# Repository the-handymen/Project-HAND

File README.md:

# Project-H.A.N.D.
H.A.N.D.: Handy Appendage for Nonlocal Distances

See it in action!
https://www.jonathankornich.com/h-a-n-d-handy-appendage-for-nonloca

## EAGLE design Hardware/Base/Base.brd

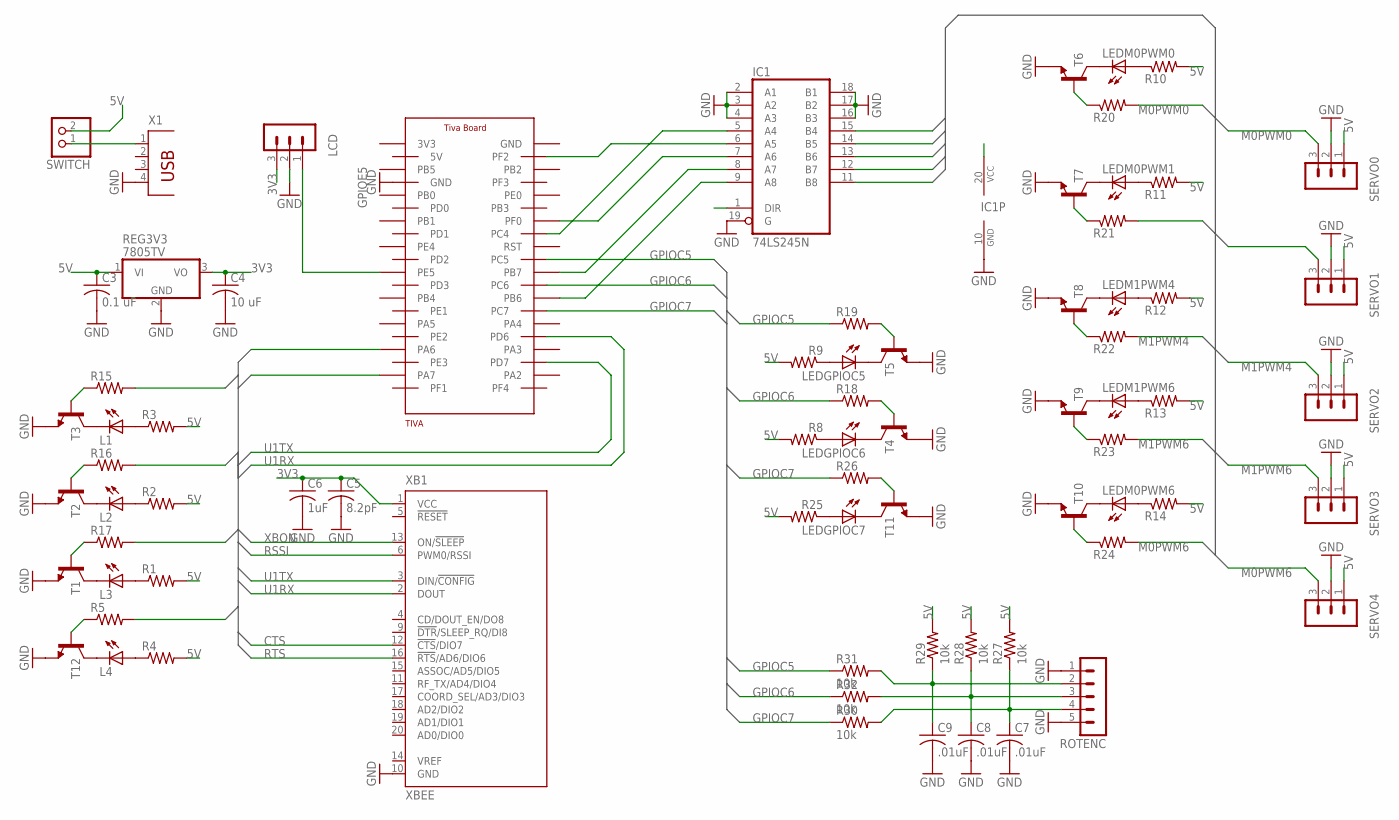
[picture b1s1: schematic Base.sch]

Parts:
C3: 0.1 uF; C025-025X050
C4: 10 uF; C025-025X050
C5: 8.2pF; C025-025X050
C6: 1uF; C025-025X050
C7, C8, C9: .01uF; C025-025X050
IC1: 74LS245N; DIL20
L1, L2, L3, L4: LED5MM
LCD: MA03-1
LEDGPIOC5, LEDGPIOC6, LEDGPIOC7: LED5MM
LEDM0PWM0, LEDM0PWM1, LEDM0PWM6, LEDM1PWM4, LEDM1PWM6: LED5MM
R1, R2, R3, R4, R5, R8, R9, R10, R11, R12, R13, R14, R15, R16, R17, R18, R19, R20, R21, R22, R23, R24, R25, R26: R-US_0207/7; 0207/7
R27, R28, R29, R30, R31, R32: 10k; 0207/7
REG3V3: 7805TV; TO220V
ROTENC: MA05-1
SERVO0, SERVO1, SERVO2, SERVO3, SERVO4: MA03-1
SWITCH: PINHD-1X2; 1X02
T1, T2, T3, T4, T5, T6, T7, T8, T9, T10, T11, T12: 2N3904; TO92
TIVA: TIVA-BOARD
X1: PN87520
XB1: XBEE

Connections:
3V3: C4.1, C5.1, C6.1, LCD.3, REG3V3.3 (VO), XB1.1 (VCC)
5V: C3.1, IC1.1 (DIR), IC1.20 (VCC), R1.2, R2.2, R3.2, R4.2, R8.2, R9.2, R10.2, R11.2, R12.2, R13.2, R14.2, R25.2, R27.2, R28.2, R29.2, REG3V3.1 (VI), SERVO0.1, SERVO1.1, SERVO2.1, SERVO3.1, SERVO4.1, SWITCH.2
CTS: TIVA.PA6, XB1.12 (!CTS!/DIO7)
GND: C3.2, C4.2, C5.2, C6.2, C7.2, C8.2, C9.2, IC1.2 (A1), IC1.3 (A2), IC1.4 (A3), IC1.10 (GND), IC1.16 (B3), IC1.17 (B2), IC1.18 (B1), IC1.19 (G), LCD.2, REG3V3.2 (GND), ROTENC.1, ROTENC.5, SERVO0.2, SERVO1.2, SERVO2.2, SERVO3.2, SERVO4.2, T1.3 (E), T2.3 (E), T3.3 (E), T4.3 (E), T5.3 (E), T6.3 (E), T7.3 (E), T8.3 (E), T9.3 (E), T10.3 (E), T11.3 (E), T12.3 (E), TIVA.GND@1 (GND), X1.4, XB1.10 (GND)
GPIOC5: R19.1, R31.1, TIVA.PC5
GPIOC6: R18.1, R32.1, TIVA.PC6
GPIOC7: R26.1, R30.1, TIVA.PC7
GPIOE5: LCD.1, TIVA.PE5
M0PWM0: IC1.11 (B8), R20.2, SERVO0.3
M0PWM1: IC1.12 (B7), R21.2, SERVO1.3
M0PWM6: IC1.15 (B4), R24.2, SERVO4.3
M1PWM4: IC1.13 (B6), R22.2, SERVO2.3
M1PWM6: IC1.14 (B5), R23.2, SERVO3.3
unnamed: L3.K (C), T1.1 (C)
unnamed: L2.K (C), T2.1 (C)
unnamed: L2.A, R2.1
unnamed: L3.A, R1.1
unnamed: L1.K (C), T3.1 (C)
unnamed: L1.A, R3.1
unnamed: SWITCH.1, X1.1
unnamed: IC1.8 (A7), TIVA.PB7
unnamed: LEDGPIOC6.K (C), T4.1 (C)
unnamed: LEDGPIOC6.A, R8.1
unnamed: LEDGPIOC5.K (C), T5.1 (C)
unnamed: LEDGPIOC5.A, R9.1
unnamed: LEDM0PWM0.K (C), T6.1 (C)
unnamed: LEDM0PWM0.A, R10.1
unnamed: LEDM0PWM1.K (C), T7.1 (C)
unnamed: LEDM0PWM1.A, R11.1
unnamed: LEDM1PWM4.K (C), T8.1 (C)
unnamed: LEDM1PWM4.A, R12.1
unnamed: LEDM1PWM6.K (C), T9.1 (C)
unnamed: LEDM1PWM6.A, R13.1
unnamed: LEDM0PWM6.K (C), T10.1 (C)
unnamed: LEDM0PWM6.A, R14.1
unnamed: R24.1, T10.2 (B)
unnamed: R23.1, T9.2 (B)
unnamed: R22.1, T8.2 (B)
unnamed: R21.1, T7.2 (B)
unnamed: R20.1, T6.2 (B)
unnamed: R15.1, T3.2 (B)
unnamed: R16.1, T2.2 (B)
unnamed: R17.1, T1.2 (B)
unnamed: R18.2, T4.2 (B)
unnamed: R19.2, T5.2 (B)
unnamed: LEDGPIOC7.K (C), T11.1 (C)
unnamed: LEDGPIOC7.A, R25.1
unnamed: R26.2, T11.2 (B)
unnamed: C7.1, R27.1, R30.2, ROTENC.4
unnamed: C8.1, R28.1, R32.2, ROTENC.3
unnamed: C9.1, R29.1, R31.2, ROTENC.2
unnamed: IC1.9 (A8), TIVA.PB6
unnamed: IC1.6 (A5), TIVA.PF2
unnamed: L4.K (C), T12.1 (C)
unnamed: L4.A, R4.1
unnamed: R5.1, T12.2 (B)
unnamed: IC1.7 (A6), TIVA.PF0
unnamed: IC1.5 (A4), TIVA.PC4
RSSI: R5.2, XB1.6 (PWM0/RSSI)
RTS: TIVA.PA7, XB1.16 (!RTS!/AD6/DIO6)
U1RX: R16.2, TIVA.PD6, XB1.2 (DOUT)
U1TX: R17.2, TIVA.PD7, XB1.3 (DIN/!CONFIG)
XBON: R15.2, XB1.13 (ON/!SLEEP)

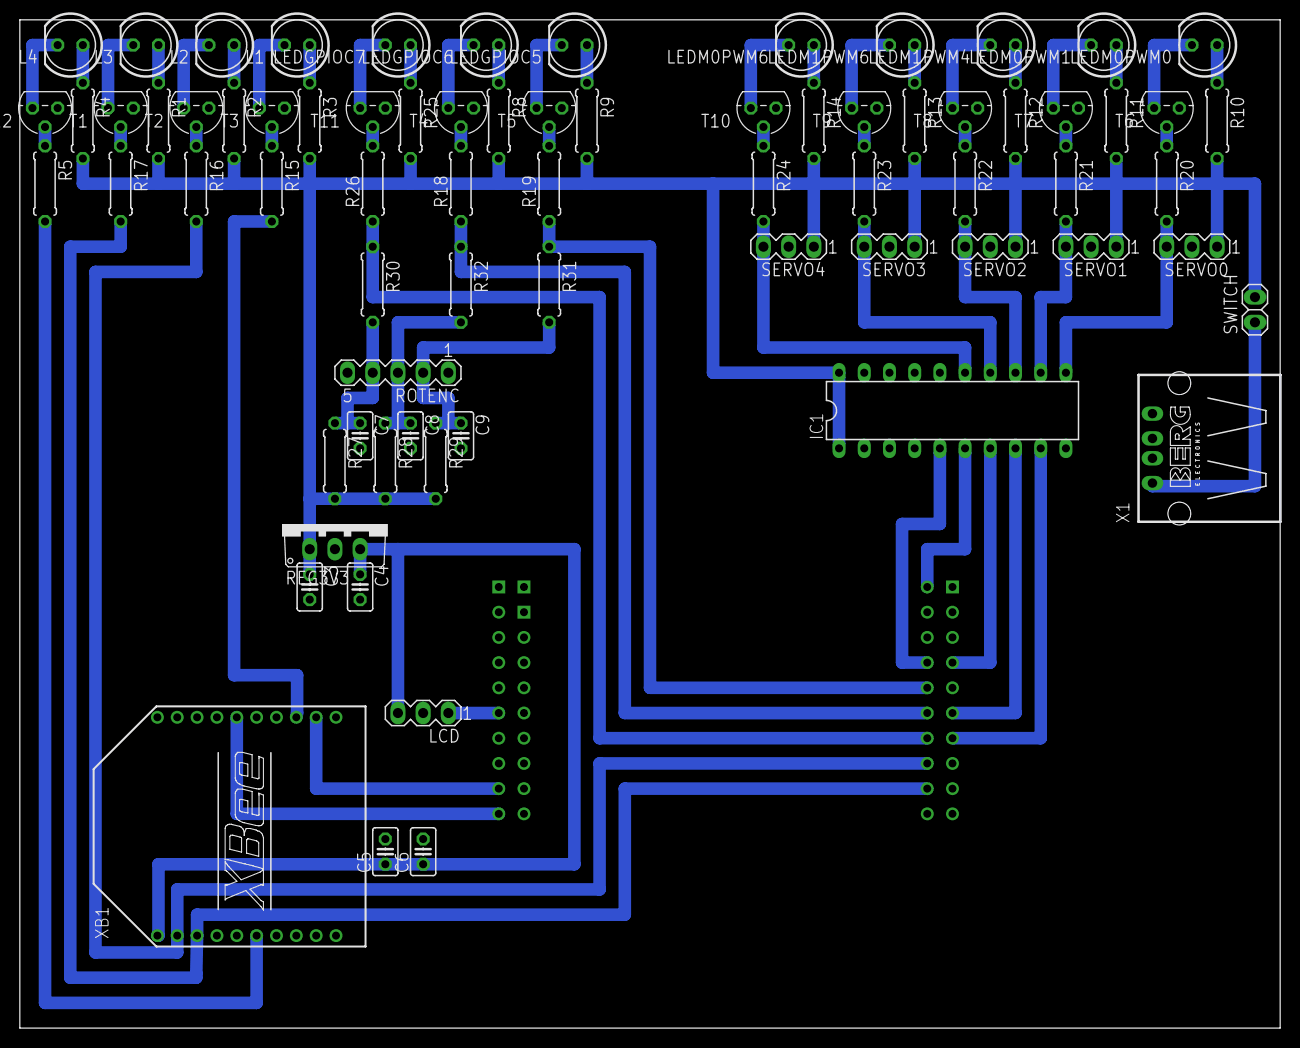
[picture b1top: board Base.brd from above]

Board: 2 copper layers, 127.0 x 101.6 mm, 74 parts (0 on the bottom side), 63 nets.

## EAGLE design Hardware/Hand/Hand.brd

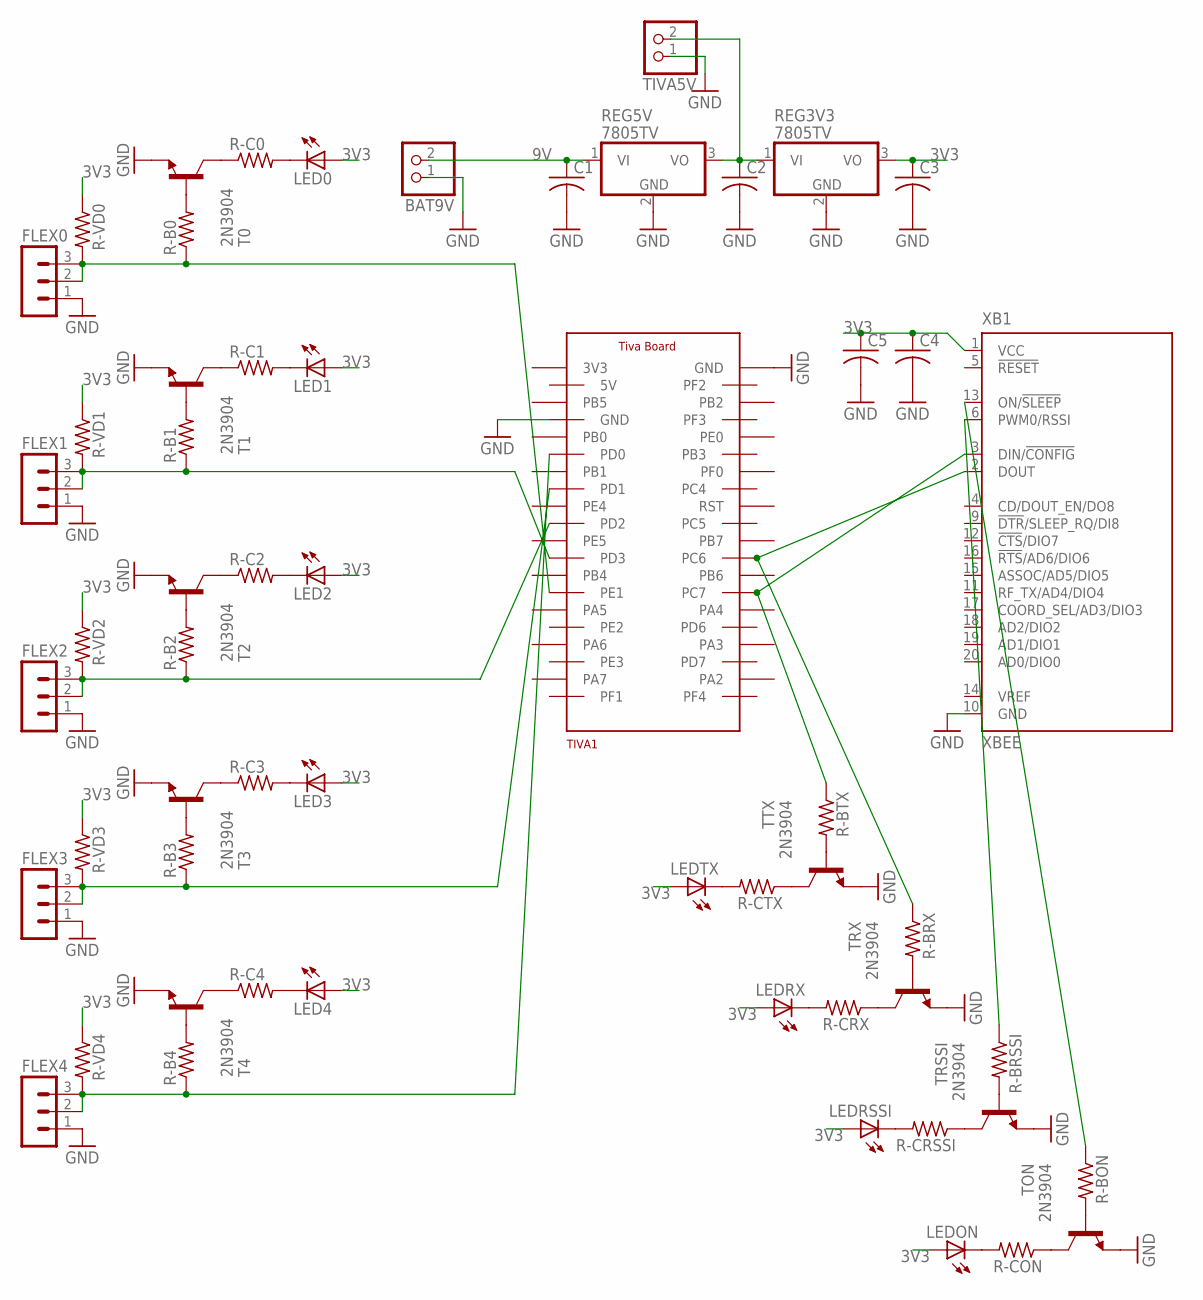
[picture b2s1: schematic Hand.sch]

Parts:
BAT9V: PINHD-1X2; 1X02
C1, C2, C3, C4, C5: C-US025-025X050; C025-025X050
FLEX0, FLEX1, FLEX2, FLEX3, FLEX4: MA03-1
LED0, LED1, LED2, LED3, LED4: LED5MM
LEDON: LED5MM
LEDRSSI: LED5MM
LEDRX: LED5MM
LEDTX: LED5MM
R-B0, R-B1, R-B2, R-B3, R-B4: R-US_0204/7; 0204/7
R-BON: R-US_0204/7; 0204/7
R-BRSSI: R-US_0204/7; 0204/7
R-BRX: R-US_0204/7; 0204/7
R-BTX: R-US_0204/7; 0204/7
R-C0, R-C1, R-C2, R-C3, R-C4: R-US_0204/7; 0204/7
R-CON: R-US_0204/7; 0204/7
R-CRSSI: R-US_0204/7; 0204/7
R-CRX: R-US_0204/7; 0204/7
R-CTX: R-US_0204/7; 0204/7
R-VD0, R-VD1, R-VD2, R-VD3, R-VD4: R-US_0204/7; 0204/7
REG3V3, REG5V: 7805TV; TO220V
T0, T1, T2, T3, T4: 2N3904; TO92
TIVA1: TIVA-BOARD
TIVA5V: PINHD-1X2; 1X02
TON: 2N3904; TO92
TRSSI: 2N3904; TO92
TRX: 2N3904; TO92
TTX: 2N3904; TO92
XB1: XBEE

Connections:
3V3: C3.1, C4.1, C5.1, LED0.A, LED1.A, LED2.A, LED3.A, LED4.A, LEDON.A, LEDRSSI.A, LEDRX.A, LEDTX.A, R-VD0.1, R-VD1.1, R-VD2.1, R-VD3.1, R-VD4.1, REG3V3.3 (VO), XB1.1 (VCC)
5V: C2.1, REG3V3.1 (VI), REG5V.3 (VO), TIVA5V.2
9V: BAT9V.2, C1.1, REG5V.1 (VI)
GND: BAT9V.1, C1.2, C2.2, C3.2, C4.2, C5.2, FLEX0.1, FLEX1.1, FLEX2.1, FLEX3.1, FLEX4.1, REG3V3.2 (GND), REG5V.2 (GND), T0.3 (E), T1.3 (E), T2.3 (E), T3.3 (E), T4.3 (E), TIVA1.GND@1 (GND), TIVA1.GND@2 (GND), TIVA5V.1, TON.3 (E), TRSSI.3 (E), TRX.3 (E), TTX.3 (E), XB1.10 (GND)
unnamed: FLEX0.2, FLEX0.3, R-B0.1, R-VD0.2, TIVA1.PE1
unnamed: R-C1.1, T1.1 (C)
unnamed: LED1.K (C), R-C1.2
unnamed: R-C2.1, T2.1 (C)
unnamed: R-B0.2, T0.2 (B)
unnamed: R-C3.1, T3.1 (C)
unnamed: LED3.K (C), R-C3.2
unnamed: R-C4.1, T4.1 (C)
unnamed: FLEX1.2, FLEX1.3, R-B1.1, R-VD1.2, TIVA1.PD3
unnamed: R-B1.2, T1.2 (B)
unnamed: LED4.K (C), R-C4.2
unnamed: LED2.K (C), R-C2.2
unnamed: FLEX2.2, FLEX2.3, R-B2.1, R-VD2.2, TIVA1.PD2
unnamed: R-B2.2, T2.2 (B)
unnamed: R-C0.1, T0.1 (C)
unnamed: LED0.K (C), R-C0.2
unnamed: FLEX3.2, FLEX3.3, R-B3.1, R-VD3.2, TIVA1.PD1
unnamed: R-B3.2, T3.2 (B)
unnamed: R-BTX.1, TIVA1.PC7, XB1.3 (DIN/!CONFIG)
unnamed: R-BRX.1, TIVA1.PC6, XB1.2 (DOUT)
unnamed: FLEX4.2, FLEX4.3, R-B4.1, R-VD4.2, TIVA1.PD0
unnamed: R-B4.2, T4.2 (B)
unnamed: R-BTX.2, TTX.2 (B)
unnamed: R-CTX.1, TTX.1 (C)
unnamed: LEDTX.K (C), R-CTX.2
unnamed: R-BRX.2, TRX.2 (B)
unnamed: R-CRX.1, TRX.1 (C)
unnamed: LEDRX.K (C), R-CRX.2
unnamed: R-BRSSI.1, XB1.6 (PWM0/RSSI)
unnamed: R-BON.1, XB1.13 (ON/!SLEEP)
unnamed: R-BRSSI.2, TRSSI.2 (B)
unnamed: R-CRSSI.1, TRSSI.1 (C)
unnamed: LEDRSSI.K (C), R-CRSSI.2
unnamed: R-BON.2, TON.2 (B)
unnamed: R-CON.1, TON.1 (C)
unnamed: LEDON.K (C), R-CON.2

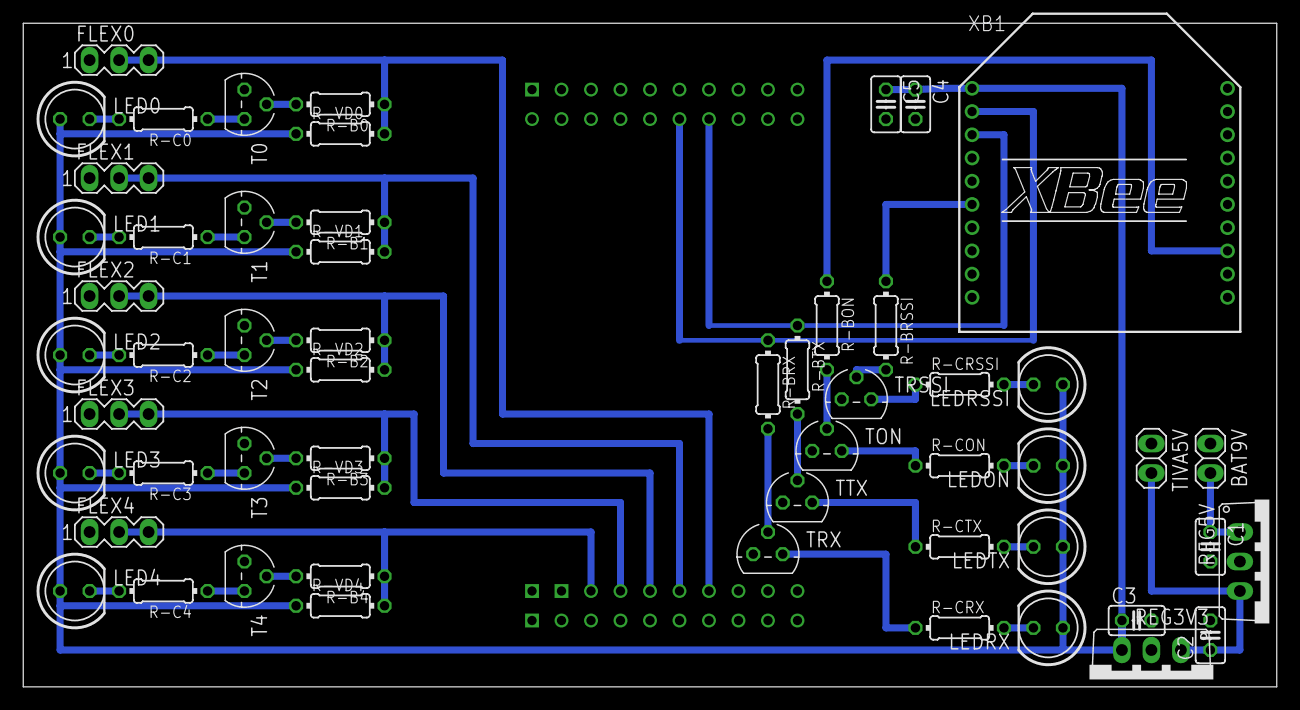
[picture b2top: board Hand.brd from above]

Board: 2 copper layers, 108.0 x 57.1 mm, 57 parts (0 on the bottom side), 40 nets.

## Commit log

2018-09-28 Add files via upload
    CAD design of the base.
2018-09-28 Move Base.scad to CAD/.
2018-09-28 Implement initial fustrum.scad.
2018-09-30 Design initial Tiva Board device.
2018-10-01 Begin Base.sch.
    Place Tiva Board.
    Created busses for I/O to Tiva Board.
2018-10-02 Now utilizes Fustrum module, wall thickness settings of top/bottom/sides now supported. Prettying up soon to come!
2018-10-02 LCD cutout included
2018-10-03 Add Xbee to base schematic.
    Add status LEDs to Tiva/Xbee communication.
2018-10-04 Add rotary encoder to base schematic.
2018-10-04 Documentation and Rotary Encoder Added
2018-10-04 Add servos to base schematic.
2018-10-08 Added power supplies.
2018-10-08 Finished rev0 base schematic.
    Created board file.
2018-10-09 Add Power cutouts, seperate parameters
    USB connector and power switch cutouts have been added, documentation updated as well.
    Parameters have been seperated into their own file (BaseParameters.scad).
2018-10-09 Lay out components of base PCB rev0.
2018-10-11 Files reordered, Finger1 begun
    All base-related .scad files have been moved into the "Base" folder
    all hand-related .scad files will be stored in the "Hand" folder.
    The first component of the fingers "finger1" has been created. Documentation soon to come.
2018-10-11 Resolution lowered for faster rendering
2018-10-15 Initial layout of traces.
    Updated power pins on Tiva Board device.
    Added most traces (except Xbee connections and a few others).
2018-10-16 Document Finger1.scad
    Finger1.scad is now fully documented
2018-10-18 I HAVE TO COMMIT BEFORE COMPUTER DIES AAAAH
2018-10-18 Add level shifter.
2018-10-18 Begin Xbee connections.
2018-10-18 2 Top Cutouts added to base
2018-10-18 All nubs added
2018-10-21 Connection changes made
    Base: Now takes SCALE, TOPLENGTH, and TOPWIDTH values from external file "connect.scad", to keep values between base.scad and hand.scad consistent.
    Base now has 5 holes cut out on the back side to allow for servo wire routing
    hand: connecting structure finished, palm yet to come.
    finger1: added variable OPEN, which allows control over whether the top is cut out to allow for a connector or not.
2018-10-21 No airwires.
2018-10-21 First printable.
2018-10-23 Hand Development
    Hand structure developed
2018-10-25 Update hand.scad
    servo cutouts added
2018-10-26 Update hand.scad
    Servo cutouts updated
2018-10-26 Update hand/base.scad
    Servo cutout spacing modified, hand is now a right hand.
2018-10-27 Update hand.scad
    Code cleaned up, thumb servo mount began
2018-10-29 hand.scad finished
2018-11-01 Fixed Tiva dimensions.
2018-11-01 Real Life Values added
2018-11-01 Added LCD screw holes
2018-11-07 Real World Value changes
    All of the CAD files now have real world values (mm) for their dimensions.
2018-11-08 Create setup and loop function skeletons.
2018-11-12 Added initial implementations of PWM and QEI modules.
2018-11-12 Added TODO for PWM.
2018-11-12 Wires prettied up in Base.brd/sch
2018-11-13 Add basic hand schematic
2018-11-13 Fixed power source in Hand.sch
2018-11-18 All servos now work. Made UART files (unimplemented).
2018-11-18 Implemented SysTick library.
2018-11-18 Deleted unused code.
2018-11-19 Hand PCB Rev0 complete.
2018-11-22 Adjust positions for milling.
2018-11-24 Read 5 ADC channels at once.
2018-11-25 UART for LCD implemented.
2018-11-25 First implementation LCD library complete.
2018-11-25 ADC-LCD snippet. ADC bug fix.
    Bug fix: ADC channels were read in a near-random order.
2018-11-26 Generalized UART library for use with any UART.
    RX untested.
2018-11-26 Implement UART_ReadChar.
    Works with UART0 at least. Different port will be tested when communicating between two Tivas.
2018-11-26 Send data from one Tiva and display from another.
2018-11-27 Move base code to base-logic.c.
2018-11-29 Bend legit fingers.
2018-12-04 Misc fixes.
2018-12-05 Basic RPS working and code refactored.
    Bug: finger order is inverted.
2018-12-05 Bug fixed.
2018-12-06 Seperated ring-pinky finger.
    We now have 5 flex sensors.
2018-12-07 Made a few screensavers.
2018-12-09 Added mode-switch.
2018-12-22 Set theme jekyll-theme-cayman
2019-10-28 Gave credit to the PRNG I found on Wikipedia.
2019-10-28 Added link to media.
